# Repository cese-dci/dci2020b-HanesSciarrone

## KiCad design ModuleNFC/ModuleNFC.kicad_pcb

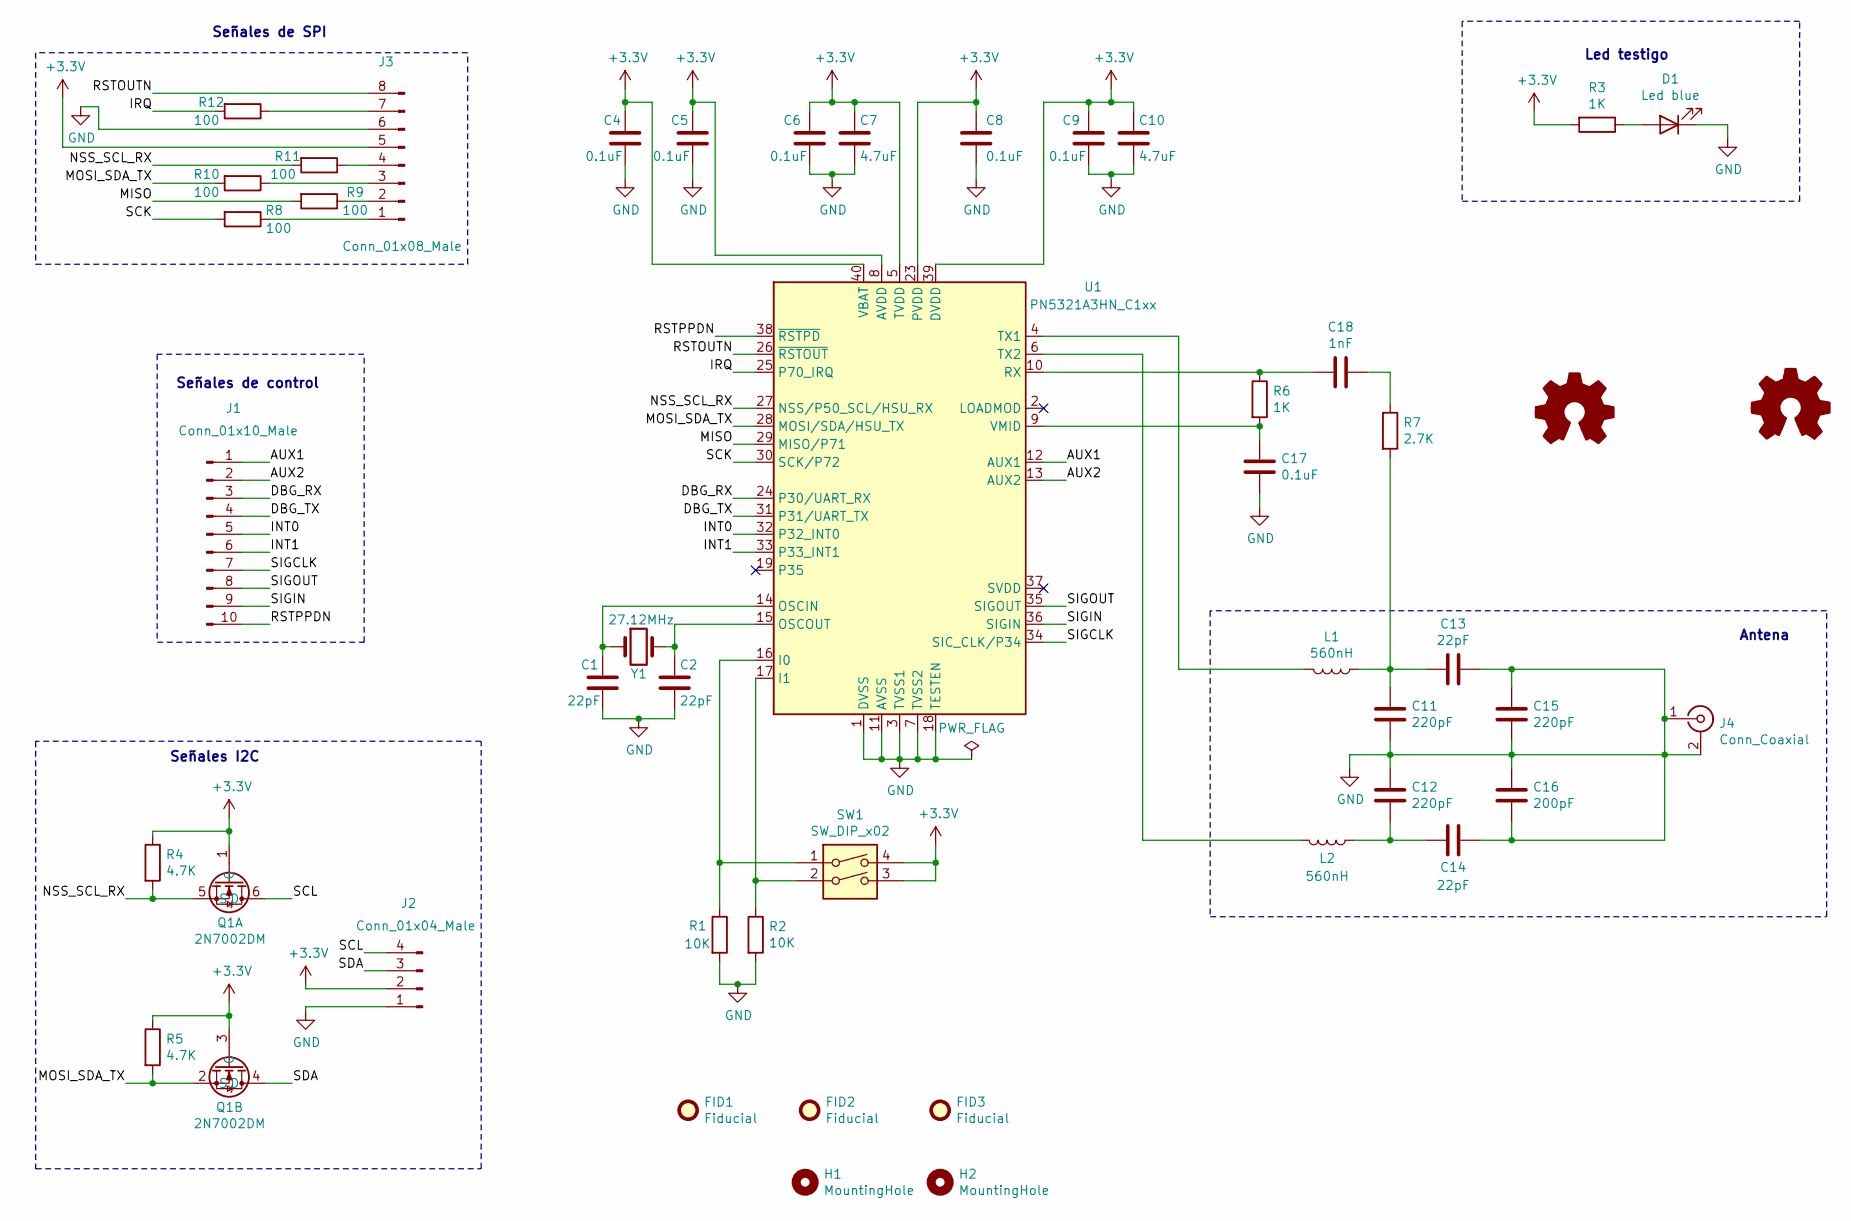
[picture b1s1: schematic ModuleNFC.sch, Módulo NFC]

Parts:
C1, C2, C13, C14: 22pF; C_0805_2012Metric
C4, C5, C6, C8, C9, C17: 0.1uF; C_0805_2012Metric
C7, C10: 4.7uF; C_0805_2012Metric
C11, C12, C15: 220pF; C_0805_2012Metric
C16: 200pF; C_0805_2012Metric
C18: 1nF; C_0805_2012Metric
D1: Led blue; LED_0603_1608Metric
FID1, FID2, FID3: Fiducial; Fiducial_1mm_Mask2mm
H1, H2: MountingHole; MountingHole_2.2mm_M2_Pad_Via
J1: Conn_01x10_Male; PinHeader_1x10_P1.00mm_Vertical
J2: Conn_01x04_Male; PinHeader_1x04_P1.27mm_Horizontal
J3: Conn_01x08_Male; PinHeader_1x08_P1.27mm_Horizontal
J4: Conn_Coaxial; U.FL_Molex_MCRF_73412-0110_Vertical; Part Number 538-73412-0110
L1, L2: 560nH; L_1008_2520Metric
LOGO1: Logo_Open_Hardware_Small; OSHW-Logo2_7.3x6mm_SilkScreen
LOGO2: Logo_Open_Hardware_Small; KiCad-Logo2_5mm_Copper
Q1: 2N7002DM; SC-74-6_1.5x2.9mm_P0.95mm
R1, R2: 10K; R_0805_2012Metric
R3, R6: 1K; R_0805_2012Metric
R4, R5: 4.7K; R_0805_2012Metric
R7: 2.7K; R_0805_2012Metric
R8, R9, R10, R11, R12: 100; R_0805_2012Metric
SW1: SW_DIP_x02; SW_DIP_SPSTx02_Slide_KingTek_DSHP02TS_W7.62mm_P1.27mm; Part Number CT3108CT-ND
U1: PN5321A3HN_C1xx; HVQFN-40-1EP_6x6mm_P0.5mm_EP4.1x4.1mm; Part Number 568-13228-ND
Y1: 27.12MHz; Crystal_SMD_0603-2Pin_6.0x3.5mm; Part Number XC1671TR-ND

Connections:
+3V3: C4.1, C5.1, C6.1, C7.1, C8.1, C9.1, C10.1, J2.2, J3.5, Q1.1 (G), Q1.3 (G), R3.2, R4.1, R5.1, SW1.3, SW1.4, U1.5 (TVDD), U1.8 (AVDD), U1.23 (PVDD), U1.39 (DVDD), U1.40 (VBAT)
/AUX1: J1.1, U1.12 (AUX1)
/AUX2: J1.2, U1.13 (AUX2)
/DBG_RX: J1.3, U1.24 (P30/UART_RX)
/DBG_TX: J1.4, U1.31 (P31/UART_TX)
/INT0: J1.5, U1.32 (P32_INT0)
/INT1: J1.6, U1.33 (P33_INT1)
/IRQ: R12.2, U1.25 (P70_IRQ)
/MISO: R9.2, U1.29 (MISO/P71)
/MOSI_SDA_TX: Q1.2 (S), R5.2, R10.2, U1.28 (MOSI/SDA/HSU_TX)
/NSS_SCL_RX: Q1.5 (S), R4.2, R11.2, U1.27 (NSS/P50_SCL/HSU_RX)
/RSTOUTN: J3.8, U1.26 (~RSTOUT)
/RSTPPDN: J1.10, U1.38 (~RSTPD)
/SCK: R8.2, U1.30 (SCK/P72)
/SCL: J2.4, Q1.6 (D)
/SDA: J2.3, Q1.4 (D)
/SIGCLK: J1.7, U1.34 (SIC_CLK/P34)
/SIGIN: J1.9, U1.36 (SIGIN)
/SIGOUT: J1.8, U1.35 (SIGOUT)
GND: C1.2, C2.2, C4.2, C5.2, C6.2, C7.2, C8.2, C9.2, C10.2, C11.2, C12.1, C13.1, C14.1, C15.1, C15.2, C16.1, C16.2, C17.2, D1.1 (K), J2.1, J3.6, J4.1 (In), J4.2 (Ext), R1.2, R2.2, U1.1 (DVSS), U1.3 (TVSS1), U1.7 (TVSS2), U1.11 (AVSS), U1.18 (TESTEN), U1.41 (AVSS)
unnamed: C1.1, U1.14 (OSCIN), Y1.1
unnamed: C2.1, U1.15 (OSCOUT), Y1.2
unnamed: C11.1, C13.2, L1.1, R7.2
unnamed: C12.2, C14.2, L2.1
unnamed: C17.1, R6.2, U1.9 (VMID)
unnamed: C18.1, R7.1
unnamed: C18.2, R6.1, U1.10 (RX)
unnamed: D1.2 (A), R3.1
unnamed: J3.1, R8.1
unnamed: J3.2, R9.1
unnamed: J3.3, R10.1
unnamed: J3.4, R11.1
unnamed: J3.7, R12.1
unnamed: L1.2, U1.4 (TX1)
unnamed: L2.2, U1.6 (TX2)
unnamed: R1.1, SW1.1, U1.16 (I0)
unnamed: R2.1, SW1.2, U1.17 (I1)

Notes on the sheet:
Led testigo
Señales de control
Señales I2C
Antena
Señales de SPI

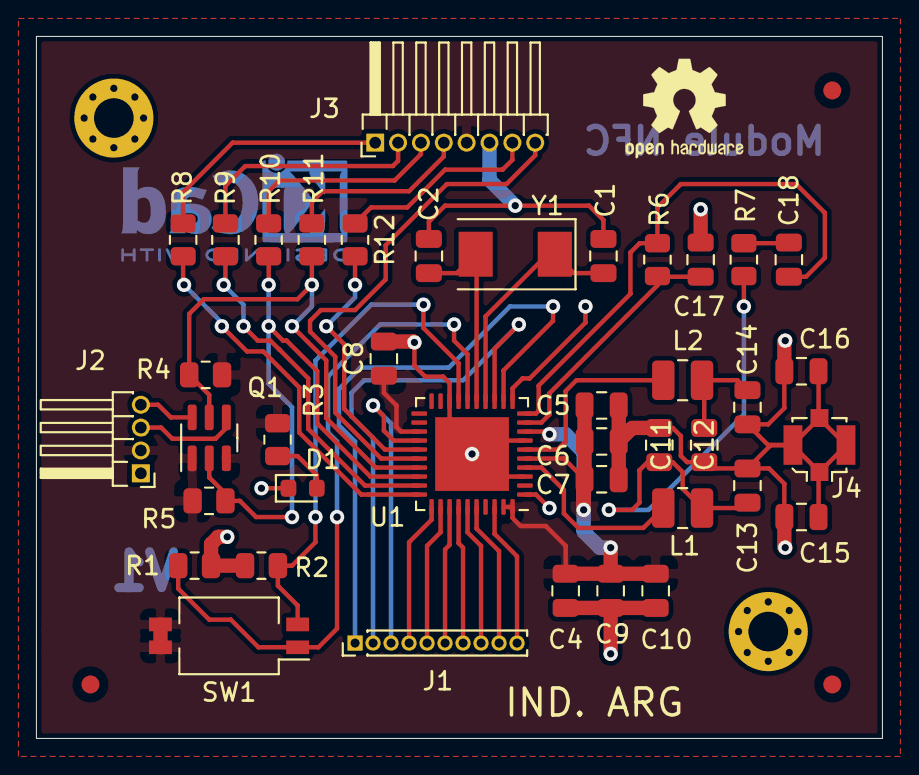
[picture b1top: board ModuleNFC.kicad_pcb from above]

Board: 2 copper layers, 47.0 x 39.0 mm, 47 parts (1 on the bottom side), 37 nets.

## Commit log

2020-09-28 Schematic with Module NFC
2020-10-01 Esquemático y PCB versión 1
2020-10-03 Board modificaed
2020-10-03 Added dimensions
2020-10-07 Added comment at margin with parameters of PCB
2020-10-07 Add model 3D of PN532
2020-10-16 Modification on PCB and Schematic on base of correction
2020-10-17 All modification with correction
2020-10-23 Export model 3D
2020-10-24 Reference of symbol, footprint and model 3D on relative way
2020-11-04 Second revision of PCB and schematic, first change
2020-11-13 Correction final v1
2020-11-13 Cambios en el rotulo
2020-11-14 Last version of correction

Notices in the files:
ModuleNFC/ModuleNFC.kicad_pcb:
Licencia: CERN Open Hardware License Version 2 Permissive
